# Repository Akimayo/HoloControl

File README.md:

# &nbsp;HoloControl

## Obsah
- [ HoloControl](#holocontrol)
  - [Obsah](#obsah)
  - [Úvod](#úvod)
  - [Rychlý manuál](#rychlý-manuál)
    - [Ovládání fyzickými tlačítky v manuálním režimu](#ovládání-fyzickými-tlačítky-v-manuálním-režimu)
    - [Ovládání fyzickými tlačítky v automatickém režimu](#ovládání-fyzickými-tlačítky-v-automatickém-režimu)
  - [Zapojování elektronického obvodu](#zapojování-elektronického-obvodu)
  - [Zdrojový kód](#zdrojový-kód)

## Úvod
Sada HoloControl slouží k řízení laserových zdrojů pro účely holografie. Skládá se z programu pro Raspberry Pi Pico pro samotné řízení, elektronického obvodu pro napájení, indikaci a ovládání a (semi-)grafického rozhraní pro Windows a Android.

Tato sada byla vytvořena v rámci studentského projektu na MFF UK pro zjednodušení holografického experimentu.

## Rychlý manuál
> Předpokládá se, že již máte nainstalovanou aplikaci _HoloControl_ na svém zařízení. Pokud ne, můžete ji stáhnout [zde](https://update.mciesla.cz/HoloControl).
1. Připojte USB kabel z experimentu do svého zařízení
2. Zapojte zásuvkový adaptér z experimentu do elektrické sítě  
   > [!IMPORTANT]
   > Pořadí je zde důležité: Pokud zapojíte experiment do elektrické sítě dříve, než do svého počítače, všechny lasery se zapnou, což může přinést riziko osvícení intenzivním laserovým zářením.
3. Spusťte aplikaci _HoloControl_ na svém zařízení
4. Vlevo nahoře vyberte port, na kterém je experiment připojen, a klikněte na tlačítko připojit.  
   > [!TIP]
   > Pokud nevíte, na kterém portu je experiment připojen, můžete buďto aplikaci spustit před připojením experimentu ke svému zařízení a sledovat, který port přibyl, nebo postupně porty v seznamu vyzkoušet. Aplikace vždy nejprve ověří, zda se na daném portu nachází mikropočítač s programem k experimentu.
5. V konzoli aplikace se zobrazí informace o připojení a nad konzolí se změní stav připojení. V dolní části konzole se aktivuje modré tlačítko _Odeslat_.
6. Pomocí prvních tří možností zkontrolujte současné nastavení experimentu.  
   > [!NOTE]
   > Tlačítka pouze přidávají příkazy do vstupního pole konzole, klikněte na modré tlačítko pro jejich odeslání do experimentu.
7. Přepněte experiment do požadovaného režimu (automatický/manuální) fyzickým přepínačem na experimentu. Informace o ovládání fyzickými tlačítky jsou uvedeny níže. Dále jsou uvedeny kroky pro ovládání automatického režimu.
8. Nastavte požadované časy expozice v jednotlivých barvách. Nejprve vpiště hodnotu do pole vpravo, poté klikněte na tlačítko s názvem příkazu. Kliknutím na každé tlačítko se opět pouze vloží příkaz do vstupního pole konzole, odešlete (i více příkazů najednou) kliknutím na modré tlačítko.
   > [!WARNING]
   > Časy expozice se nastavují podle citlivosti holografické desky v dané barvě udané výrobcem a naměřeného výkonu laseru. K této kalibraci se využívá manuální režim.

   Můžete také nastavit čas čekání před zahájením expozice a čas dosvěcování holografické desky po dokončení expozice lasery.
9. Pokud délka USB kabelu umožňuje, abyste se svým zařízením stále připojeným opustili místnost s experimentem, můžete expozici zahájit odesláním příkazu z aplikace. Pokud ne, zhasněte displej svého zařízení (neodpojujte od experimentu!) a expozici můžete zahájit stisknutím kulatého bílého fyzického tlačítka na experimentu.  
   > [!NOTE]
   > Experiment má zabudovaný bzučák, který je spuštěn vždy na začátku a konci expozice. Bzučí při zahájení čekací doby, při zapnutí laserů, při vypnutí laserů a při vypnutí dosvětlovací světelné diody.
10. Expozice doběhne plně automaticky s nastavenými časy. Pokud potřebujete expozici přerušit, použijte kulaté bílé fyzické tlačítko nebo z aplikace odešlete příkaz. Můžete expozici buďto pozastavit (stisknutím tlačítka) nebo zrušit (podržením tlačítka alespoň $2\,\text{s}$).

### Ovládání fyzickými tlačítky v manuálním režimu
- 🟨 Čtvercové žluté tlačítko přepíná mezi lasery. Aktuálně spuštěný laser je indikován světelnou diodou vlevo od tlačítka.
- ⚪ Kulaté bílé tlačítko zapíná a vypíná dosvětlovací světelnou diodu. Její stav indikuje samostatná světelná dioda mezi tlačítky.

### Ovládání fyzickými tlačítky v automatickém režimu
- 🟨 Čtvercové žluté tlačítko se nepoužívá.
- ⚪ Kulaté bílé tlačítko pozastavuje a spouští expozici. Podržením tlačítka déle než $2\,\text{s}$ resetuje expozici.

## Zapojování elektronického obvodu
Obvod se skládá ze tří desek plošných spojů spojených čtyřmi kabely.
- Deska s dosvětlovací světelnou diodu se spojuje silným dvoužilovým kabelem zapojeným do svorkovnic. Na hlavní desce je svorkovnice označena `L+`, strana s `+` je kladný pól.
- Deska řídícího panelu je připojena dvěma čtyřžilovými a jedním desetižilovým plochým kabelem. Pokud máte kabely osazené konektory, nejprve zapojte čtyřžilový kabel do obou vidlic označených `Con_SW1A`, poté zapojte zbylé kabely do odpovídajících vidlic. Pokud kabely osazené konektory nemáte nebo si nejste jistí, podívejte se na [schéma zapojení](HoloControl-PCB/README.md).
- Trojice laserů přímo v experimentu se připojuje do svorkovnic označených `R+` (červená), `G+` (zelená) a `B+` (modrá). Strana s `+` opět značí kladný pól.
- Externí laser se připojuje pomocí BNC konektoru koaxiálním kabelem (nebo přechodkou BNC-USB).

> [!CAUTION]
> Všechny napájecí výstupy (`R+`, `G+`, `B+` a `L+`) jsou připojeny na proudové regulátory. Pokud se jedná o novou desku, nebo se v experimentu měnily lasery, je nutné pomocí multimetru připojeného nakrátko do svorkovnice v režimu ampérmetru a plochého šroubováku upravit odpor trimrů, aby regulátory dávaly správný proud a nedošlo k poškození laserů.

## Zdrojový kód
Tento repozitář obsahuje zdrojový kód programu pro mikropočítač Raspberry Pi Pico v experimentu a uživatelské aplikace _HoloControl_ pro pohodlnou komunikaci s mikropočítačem.

Mikropočítač vykonává program napsaný v jazyce C s knihovnou _Pico SDK_ a nachází se v adresáři [HoloControl-Pico](HoloControl-Pico/). Vstupním bodem programu je [`i_holo_control.c::main()`](HoloControl-Pico/i_holo_controller.c#L091).

Uživatelská aplikace _HoloControl_ je napsána v jazyce C# pomocí frameworku _MAUI_ a je v principu dostupná pro platformy Windows, Android, MacOS, iOS a Tizen. V praxi jsou ale platformy MacOS, iOS a Tizen vynechány ze sestavení, jelikož pro ně nebyla poptávka. Platforma Android je sice implementována, ale s dostupnými zařízeními se na ní nepodařilo  odladit fungování sériové komunikace s mikropočítačem &mdash; v praxi je tedy použitelná pouze aplikace pro Windows. Zdrojový kód aplikace je v adresáři [HoloControl-UI](HoloControl-UI/) a vstupním bodem programu je [MauiProgram.cs::CreateMauiApp()](HoloControl-UI/MauiProgram.cs#L009).

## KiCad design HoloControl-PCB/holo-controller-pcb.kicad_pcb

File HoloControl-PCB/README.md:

# HoloControl: Zapojení elektronického obvodu

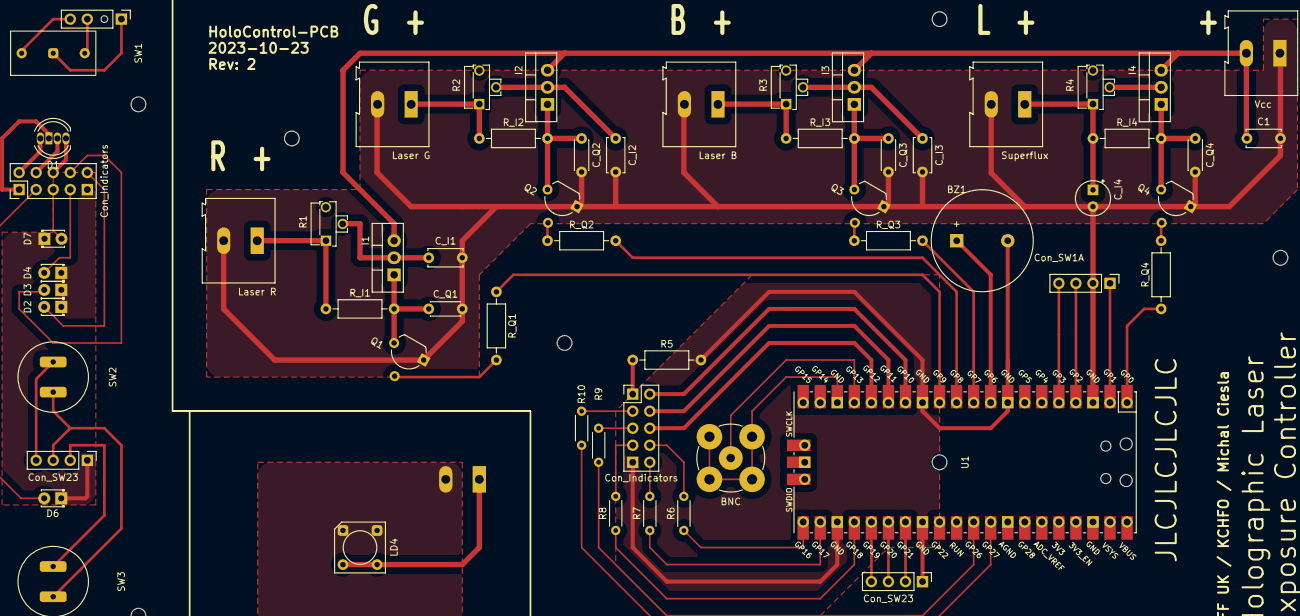
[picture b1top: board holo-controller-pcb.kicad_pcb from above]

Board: 2 copper layers, 59 parts (1 on the bottom side), 35 nets.

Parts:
-9V: TerminalBlock_Altech_AK300-2_P5.00mm
BZ1: Buzzer; Buzzer_15x7.5RM7.6
C1: 1u; C_Disc_D5.0mm_W2.5mm_P5.00mm
C_I1, C_I2, C_I3: 100n; C_Disc_D5.0mm_W2.5mm_P5.00mm
C_I4: 220u; CP_Radial_Tantal_D5.0mm_P2.50mm
C_Q1, C_Q2, C_Q3, C_Q4: 100n; C_Disc_D4.3mm_W1.9mm_P5.00mm
D1: LED_D5.0mm-4_RGB
D1#2, D1#3: Con_Indicators; PinHeader_2x05_P2.54mm_Vertical
D2, D3, D4, D6, D7: 204WC2A-W_-3P; LED_D1.8mm_W3.3mm_H2.4mm
I1, I2, I3, I4: LM317T; TO-220-3_Vertical
LD1, LD2, LD3, LD4#2, LD4#3: TerminalBlock_Altech_AK300-2_P5.00mm
LD4: OSW47LZ281P
Q1, Q2, Q3, Q4: 2N3904; TO-92_Inline_Wide
R1, R2, R3, R4: 50R; Potentiometer_Runtron_RM-063_Horizontal
R5: 4k7; R_Axial_DIN0207_L6.3mm_D2.5mm_P10.16mm_Horizontal
R6, R8, R9, R10: 10k; R_Axial_DIN0204_L3.6mm_D1.6mm_P5.08mm_Horizontal
R7: 4k7; R_Axial_DIN0204_L3.6mm_D1.6mm_P5.08mm_Horizontal
R_I1, R_I2, R_I3, R_I4: 1k; R_Axial_DIN0207_L6.3mm_D2.5mm_P10.16mm_Horizontal
R_Q1, R_Q2, R_Q3, R_Q4: 4k7; R_Axial_DIN0207_L6.3mm_D2.5mm_P10.16mm_Horizontal
SW1: B1407 Slide Switch
SW1A, SW1A#2: Con_SW1A; PinHeader_1x04_P2.54mm_Vertical
SW2, SW2#2: Con_SW23; PinHeader_1x04_P2.54mm_Vertical
SW2#3: PBS-12B Push-Button Switch
SW3: PBS-11B Push-Button Switch
U1: Pico; RPi_Pico_SMD_TH

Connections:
+9V: -9V.2, C1.1, I1.3 (VI), I2.3 (VI), I3.3 (VI), I4.3 (VI)
-9V: -9V.1, C1.2, C_I1.2, C_I2.2, C_I3.2, C_I4.2, C_Q1.2, C_Q2.2, C_Q3.2, C_Q4.2, LD1.1, LD2.1, LD3.1, LD4.1, LD4.2, LD4#2.1, LD4#3.2, Q1.1 (E), Q2.1 (E), Q3.1 (E), Q4.1 (E), SW1A#2.4, U1.3 (GND)
BZ1+: BZ1.1, U1.9 (GPIO6)
D1-B: D1.1, D1#2.6, D1#3.6, U1.16 (GPIO12)
D1-C: D1.3, D1#2.1, D1#3.1, R5.1
D1-G: D1.2, D1#2.4, D1#3.4, U1.15 (GPIO11)
D1-R: D1.4, D1#2.2, D1#3.2, U1.14 (GPIO10)
D-GND: BZ1.2, D1#2.9, D1#3.9, D2.1, D3.1, D4.1, D6.1, D7.1, R5.2, SW2.1, SW2#2.1, U1.8 (GND), U1.13 (GND), U1.23 (GND), U1.28 (GND)
I1: LD1.2, R1.1, R_I1.1
I1-Adj: C_Q1.1, I1.1 (ADJ), Q1.3 (C), R_I1.2
I1-Vo: C_I1.1, I1.2 (VO), R1.2
I2: LD2.2, R2.1, R_I2.1
I2-Adj: C_Q2.1, I2.1 (ADJ), Q2.3 (C), R_I2.2
I2-Vo: C_I2.1, I2.2 (VO), R2.2
I3: LD3.2, R3.1, R_I3.1
I3-Adj: C_Q3.1, I3.1 (ADJ), Q3.3 (C), R_I3.2
I3-Vo: C_I3.1, I3.2 (VO), R3.2
I4: C_I4.1, LD4.3, LD4.4, LD4#2.2, LD4#3.1, R4.1, R_I4.1
I4-Adj: C_Q4.1, I4.1 (ADJ), Q4.3 (C), R_I4.2
I4-Vo: I4.2 (VO), R4.2
LED-B: D1#2.7, D1#3.7, D4.2, R8.1, R8.2, U1.24 (GPIO18)
LED-G: D1#2.8, D1#3.8, D3.2, R6.1, R6.2, U1.21 (GPIO16)
LED-R: D1#2.10, D1#3.10, D2.2, R7.1, R7.2, U1.22 (GPIO17)
LED-W: D1#2.3, D1#3.3, D6.2, R10.1, R10.2, U1.32 (GPIO27_ADC1)
LED-WW: D1#2.5, D1#3.5, D7.2, R9.1, R9.2, U1.31 (GPIO26_ADC0)
Q1: Q1.2 (B), R_Q1.1, R_Q1.2, U1.12 (GPIO9)
Q2: Q2.2 (B), R_Q2.1, R_Q2.2, U1.11 (GPIO8)
Q3: Q3.2 (B), R_Q3.1, R_Q3.2, U1.10 (GPIO7)
Q4: Q4.2 (B), R_Q4.1, R_Q4.2, U1.1 (GPIO0)
SW1-A: SW1.3, SW1A.3, SW1A#2.3, U1.5 (GPIO3)
SW1-In: SW1.2, SW1A.2, SW1A#2.2, U1.2 (GPIO1)
SW1-M: SW1.1, SW1A.1, SW1A#2.1, U1.4 (GPIO2)
SW2-Out: SW2.4, SW2#2.4, SW2#3.2, U1.25 (GPIO19)
SW3-Out: SW2.2, SW2#2.2, SW3.2, U1.27 (GPIO21)
SW-In: SW2.3, SW2#2.3, SW2#3.1, SW3.1, U1.26 (GPIO20)

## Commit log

2023-10-07 Negate laser trigger outputs to accomodate new circuit
2023-10-13 Fix comments on pinout
2023-10-13 Update PCB schematic to new current regulator design
2023-10-13 Add readme intro
2023-10-13 Finish first draft of report
2023-10-30 Fix visual issues - Remove buitů-in dark mode - Fix app icon - Code cleanup
2023-11-03 Fix Pico serial communication (on Windows)
2023-11-03 Use `RelayCommand` for UI commanding - Added _CommunityToolkit.Mvvm_ package
2023-11-03 Re-implement dark mode - Revert changes to `Styles.xaml` - Update `Styles.xaml` button styling - Add white icons
2023-11-03 Update board - Includes a change to pinout of white LEDs (swapped)
2023-11-03 Add a Pico command for UI to check it is a HoloControl board
2023-11-03 Add board check when connecting from UI
2023-11-03 Fancify console log - Add response parser - Create a `HistoryItem` object - Add Phosphor Icons for info and responses - `CollectionView` is buggy, doesn't scroll and expands too much -> restricted to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
2023-11-03 Increment version number
2023-11-13 Fix serial messages and force hide status during exposition - Add a call to force shutoff status LED during exposition - Add comments to AUTO mode branches in main loop - Fix serial color message - F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
2023-11-13 Finished KiCad schematic and board
2024-08-09 Start writing electronics documentation
2024-11-23 Refresh certificate
2024-11-23 Fix typo in `Controls.Timing.Rest`[en]
2024-11-23 Add checking that a port is still open
2024-11-23 Refresh port list when picker is focused
2024-11-23 Change communication from strings to bytes - Return of `SendString(...)` is now a `byte[]` - Add back support for sending multiple commands at once - Manipulation of command text is now handled by `H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
2024-11-23 Fix sending of shortened command
2024-11-23 Make buttons only append commands to input
2024-11-23 Make status icon an actual circle
2024-11-23 Add app action for future kiosk mode
2024-11-23 Update metadata and add auto-update for Windows app
2025-11-28 Fix critical bug which caused the finishing LED to turn on together with the external laser Cause: The memory for laser exposure times was short by one `uint` and it happened to be followed directly 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
2025-11-28 Update to .NET 9.0 and MAUI 9
2025-12-01 Move from Pico SDK to Raspberry Pi Pico extension, re-initialize project
2025-12-04 Fix #4, process serial commands immediately
2025-12-04 Change output pins to fit the current board
2025-12-05 Fix #1, set height of console output window, change sending indicator, keep history scrolled to the end
2025-12-05 Fix #3, add "clear history" button and command, improve alignment of status indicator
2025-12-05 Use app shells instead of pages for app actions
2025-12-07 Implement Kiosk App Mode, only for Manual Mode for now
2025-12-07 Clean up code
2025-12-07 Rename the Publish Profile
2025-12-07 Increment version number, set autoupdate check interval to 6 hours
2025-12-11 Add parsing of time values in kiosk mode
2025-12-11 Implement commanding for start/pause/stop actions in kiosk mode
2025-12-20 Allow hiding of output window in kiosk mode, add shadow to output and port selection
2025-12-20 Finish Kiosk mode layout and functionality (automatic mode) - Update `TimeKeeper` to send `PropertyChanged` events only when the numeric value actually changes - Simplify sending commands by overridi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
2025-12-20 Remove a line of code when changing port to hopefully stop crashes
2025-12-20 Fix `KioskViewModel.RemainingTime` to return zero when `KioskViewModel._totalTime` is not set This used to perform 0/0, which returns NaN, which the `ProgressBar` did not like
2025-12-20 Add localization to kiosk mode and app actions, improve localization of standard mode - Add full localization of kiosk mode - Add tooltips to buttons in kiosk mode - Add tooltip to _clear history_ bu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
2025-12-20 Bump version number, now in release phase
2025-12-21 Fix timers in kiosk automatic mode - Fix parsing of responses to not treat start/restart/pause/stop messages as errors - Fix restarting after a pause - Add custom time formatter - Properly lock UI co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
